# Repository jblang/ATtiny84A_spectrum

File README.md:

## ATtiny Spectrum Analyzer

This is an 8-channel spectrum analyzer using ATtiny84A and an electret microphone.  The 20x gain stage of the differential ADC is used so a separate amplifier is not necessary.

The code uses a DFT algorithm by Łukasz Podkalicki.  Original code was based on his [blog post](https://blog.podkalicki.com/attiny13-disco-lights-using-dft/), but after I contacted him he kindly shared a newer version of the code which I don't believe he had published previously.  I adapted the newest code to the ATtiny84A with 8 channels and tweaked the thresholds to work with an electret microphone.

The code for an earlier experiment with the ATtiny13A is also included. The 13A doesn't include a gain stage on it's ADC so a LM386 audio amplifier was used to amplify the audio signal before passing it into the 13's ADC.

I have also designed a PCB for the ATtiny84A version but I haven't had it manufactured yet.

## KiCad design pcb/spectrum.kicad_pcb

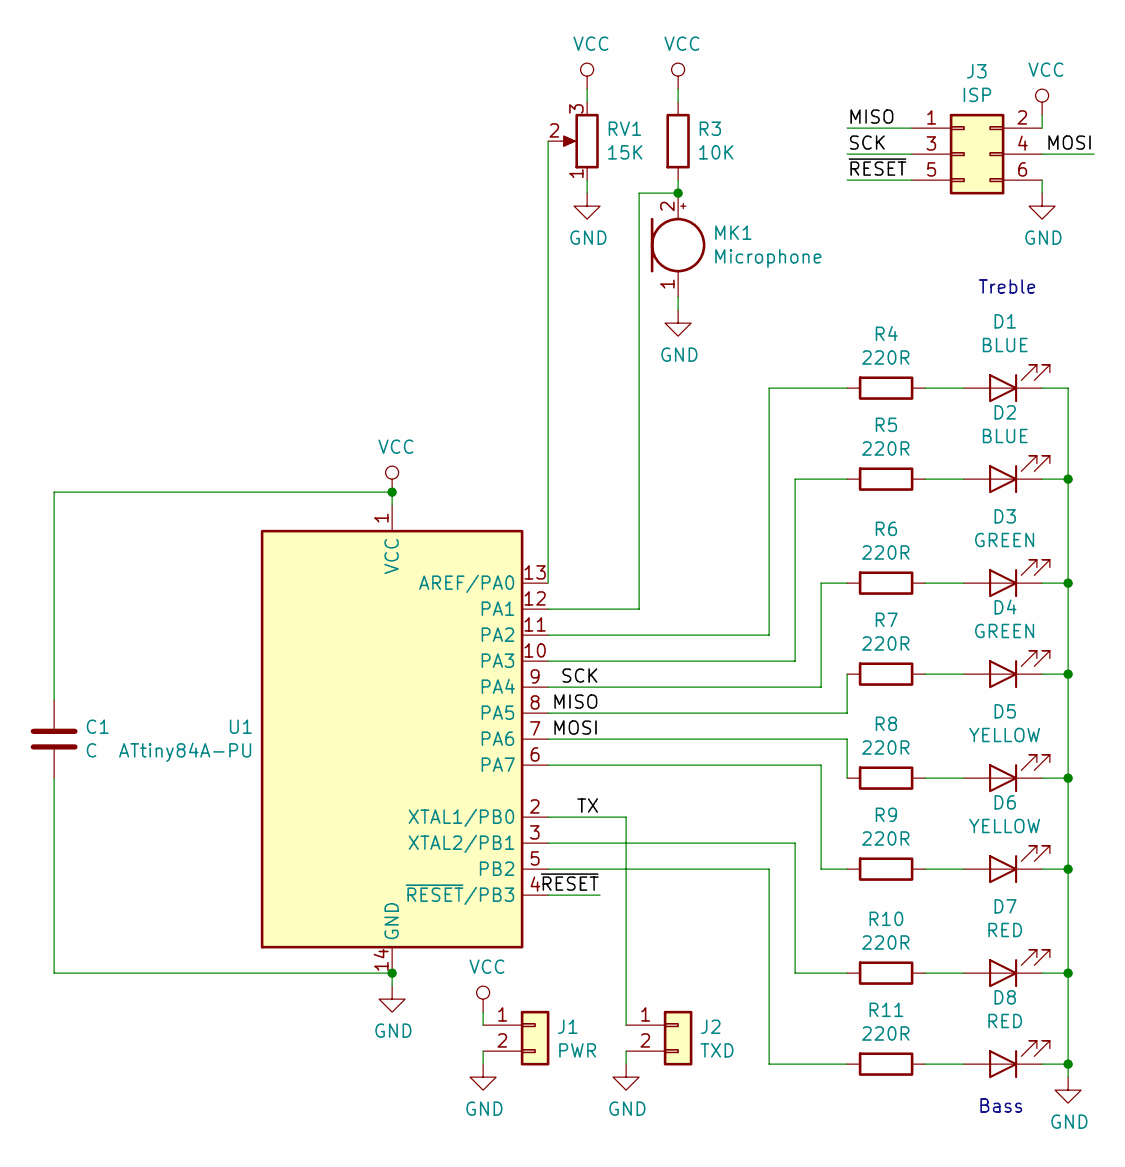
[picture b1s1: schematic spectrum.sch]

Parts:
C1: C; C_Disc_D3.0mm_W1.6mm_P2.50mm
D1, D2: BLUE; LED_D3.0mm
D3, D4: GREEN; LED_D3.0mm
D5, D6: YELLOW; LED_D3.0mm
D7, D8: RED; LED_D3.0mm
J1: PWR; PinHeader_1x02_P2.54mm_Horizontal
J2: TXD; PinHeader_1x02_P2.54mm_Horizontal
J3: ISP; PinHeader_2x03_P2.54mm_Horizontal
MK1: Microphone; PinHeader_1x02_P2.54mm_Vertical
R3: 10K; R_Axial_DIN0207_L6.3mm_D2.5mm_P7.62mm_Horizontal
R4, R5, R6, R7, R8, R9, R10, R11: 220R; R_Axial_DIN0207_L6.3mm_D2.5mm_P7.62mm_Horizontal
RV1: 15K; Potentiometer_Bourns_3296P_Horizontal
U1: ATtiny84A-PU; DIP-14_W7.62mm

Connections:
/MISO: J3.1, R7.2, U1.8 (PA5)
/MOSI: J3.4, R8.2, U1.7 (PA6)
/SCK: J3.3, R6.2, U1.9 (PA4)
/TX: J2.1, U1.2 (XTAL1/PB0)
/~RESET: J3.5, U1.4 (~RESET~/PB3)
GND: C1.2, D1.1 (K), D2.1 (K), D3.1 (K), D4.1 (K), D5.1 (K), D6.1 (K), D7.1 (K), D8.1 (K), J1.2, J2.2, J3.6, MK1.1 (-), RV1.1, U1.14 (GND)
unnamed: D1.2 (A), R4.1
unnamed: D2.2 (A), R5.1
unnamed: D3.2 (A), R6.1
unnamed: D4.2 (A), R7.1
unnamed: D5.2 (A), R8.1
unnamed: D6.2 (A), R9.1
unnamed: D7.2 (A), R10.1
unnamed: D8.2 (A), R11.1
unnamed: MK1.2 (+), R3.2, U1.12 (PA1)
unnamed: R4.2, U1.11 (PA2)
unnamed: R5.2, U1.10 (PA3)
unnamed: R9.2, U1.6 (PA7)
unnamed: R10.2, U1.3 (XTAL2/PB1)
unnamed: R11.2, U1.5 (PB2)
unnamed: RV1.2, U1.13 (AREF/PA0)
VCC: C1.1, J1.1, J3.2, R3.1, RV1.3, U1.1 (VCC)

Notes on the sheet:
Treble
Bass

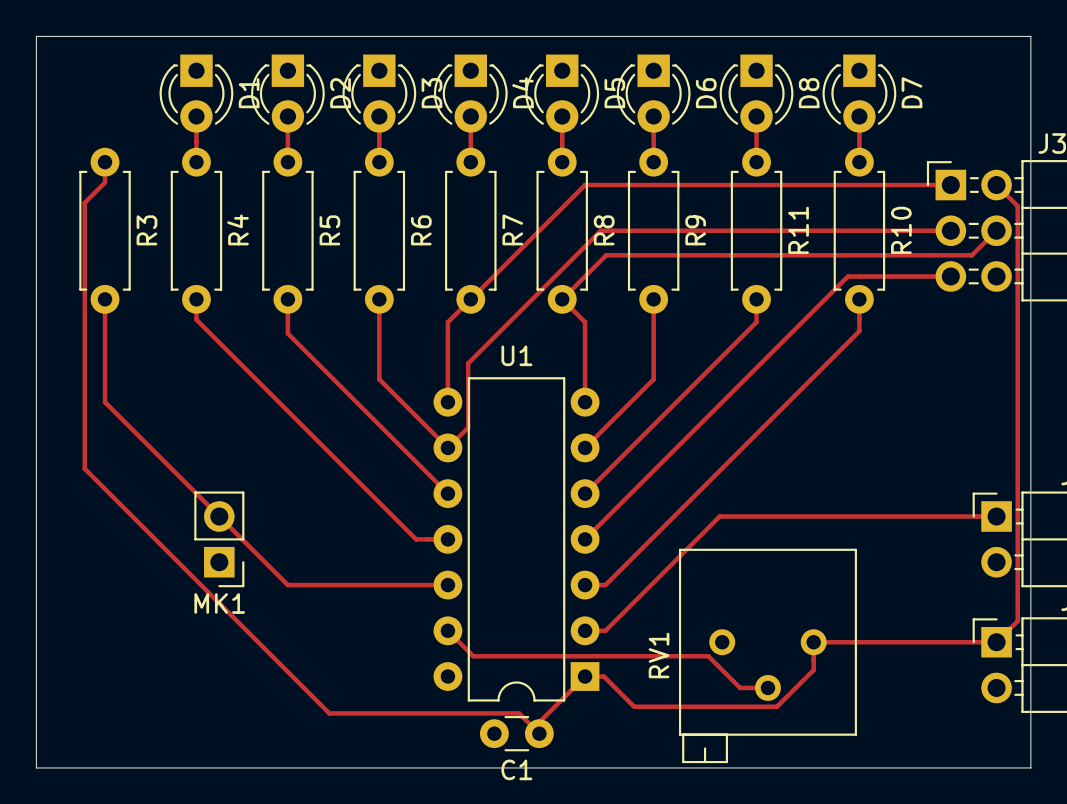
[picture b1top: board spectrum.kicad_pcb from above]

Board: 2 copper layers, 55.2 x 40.6 mm, 24 parts (0 on the bottom side), 22 nets.

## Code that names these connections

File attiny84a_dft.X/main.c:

#define F_CPU 8000000

#include <avr/io.h>
#include <avr/interrupt.h>
#include <util/delay.h>
#include <math.h>
#include <stdlib.h>

// UART pins
#define TX_PORT     PORTB
#define TX_PIN      PB0
#define TX_DDR      DDRB
#define TX_DDR_PIN  DDB0

volatile uint16_t txbyte = 0;

void uart_putchar(char c) {
    while (txbyte)
        ;
    txbyte = (c << 1) | (1 << 9); // char + stop bit
    TCCR0B = (1 << CS01);
}

void uart_putstr(char* string) {
    while (*string)
        uart_putchar(*string++);
}

void uart_init() {
    TX_DDR |= (1 << TX_DDR_PIN);
    TX_PORT |= (1 << TX_PIN);
    TCCR0A = (1 << WGM01); // CTC mode
    TIMSK0 |= (1 << OCF0A);
    OCR0A = 103; // 104 us (9600 baud ) @ 1 MHz timer clock
    sei();
}

ISR(TIM0_COMPA_vect) {
    uint16_t local_txbyte = txbyte;
    if (local_txbyte & 1)
        TX_PORT |= (1 << TX_PIN);
    else
        TX_PORT &= ~(1 << TX_PIN);
    local_txbyte >>= 1;
    txbyte = local_txbyte;
    if (!local_txbyte) {
        TCCR0B = 0;
        TCNT0 = 0;
    }
}

#define N           32
#define PI2         6.2832
#define TFS         6
#define NUM_LEDS    8
#define BANK_MAX    16
#define THRESHOLD   0U
#define OFFSET      0

static int8_t samples[N]; // discrete-time signal
static int16_t W[N]; // Twiddle Factors
static uint16_t power[NUM_LEDS + 1]; // power spectrum of x
static uint8_t bank[NUM_LEDS]; // flash accumulation
static const uint8_t pins[NUM_LEDS] = {0x11, 0x12, 0x07, 0x06, 0x05, 0x04, 0x03, 0x02};

volatile uint8_t counter = 0; // samples counter

void
dft(void) {
    int32_t Xre, Xim;
    uint8_t sin_idx, cos_idx;
    
    power[NUM_LEDS] = 0;

    for (uint8_t k = 0; k < N / 2 + 1; ++k) {
        Xre = Xim = 0;
        cos_idx = 0;
        sin_idx = 3 * N / 4;
        for (uint8_t n = 0; n < N; ++n) {
            Xre += ((int) samples[n] * (int) W[cos_idx % N]) >> TFS;
            Xim -= ((int) samples[n] * (int) W[sin_idx % N]) >> TFS;
            sin_idx += k;
            cos_idx += k;
        }
        uint16_t p = (Xre * Xre + Xim * Xim) / (N * N);
        if (k > NUM_LEDS)
            power[NUM_LEDS] = p;
        else
            power[k] = p;
    }
}

void
kolorofon(void) {
    for (uint8_t i = 0; i < NUM_LEDS; ++i) {
        if (power[i + 1] > THRESHOLD) {
            if (bank[i] < BANK_MAX) {
                bank[i]++;
            }
            if (pins[i] & 0xf0)
                PORTB |= _BV(pins[i] & 0xf);
            else
                PORTA |= _BV(pins[i] & 0xf);
        } else {
            if (bank[i]) {
                bank[i]--;
            } else {
                if (pins[i] & 0xf0)
                    PORTB &= ~_BV(pins[i] & 0xf);
                else
                    PORTA &= ~_BV(pins[i] & 0xf);
            }
        }
    }
}

ISR(ADC_vect) {

    if (counter < N) {
        samples[counter++] = ADCH; // read raw sample <-128; 127>

        ADCSRA |= _BV(ADSC); // trigger next signal acquisition
    }
}

void adc_init(void) {
    ADCSRA |= _BV(ADPS2) | _BV(ADPS1); // 8 MHz / 64 = 125 khz ADC clock
    ADCSRA |= _BV(ADEN) | _BV(ADIE); // enable ADC interrupt
    ADCSRB |= _BV(BIN) | _BV(ADLAR); // left adjust, bipolar mode
    ADMUX =  _BV(MUX3) | _BV(MUX0); // differential ADC0/1 20x gain
}

void log_power(void)
{
    for (uint8_t i = 0; i < N >> 1; i++) {
        char buf[16];
        utoa(power[i], buf, 10);
        uart_putstr(buf);
        uart_putchar('\t');
    }
    uart_putchar('\n');
    uart_putchar('\r');
}

void log_samples(void)
{
    for (uint8_t i = 0; i < N; i++) {
        char buf[16];
        itoa(samples[i], buf, 10);
        uart_putstr(buf);
        uart_putchar('\t');
    }
    uart_putchar('\n');
    uart_putchar('\r');
}

int main(void) {
    DDRB |= _BV(PB2) | _BV(PB1);
    DDRA |= _BV(PA7) | _BV(PA6) | _BV(PA5) | _BV(PA4) | _BV(PA3) | _BV(PA2);

    adc_init();
    uart_init();
    sei();

    ADCSRA |= _BV(ADSC);

    /* generate Twiddle Factors */
    for (uint8_t n = 0; n < N; ++n) {
        W[n] = (int16_t) ((float) (1 << TFS) *
                cos((float) n * PI2 / (float) N));
    }

    while (1) {
        if (counter == N) {
            dft();
            //log_power();
            //log_samples();
            kolorofon();
            counter = 0;
            ADCSRA |= _BV(ADSC);
        }
    }
}
